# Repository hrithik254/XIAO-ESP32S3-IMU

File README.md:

An IMU with MPU9250 IMU and XAIO ESP32S3  # XIAO-ESP32S3-IMU

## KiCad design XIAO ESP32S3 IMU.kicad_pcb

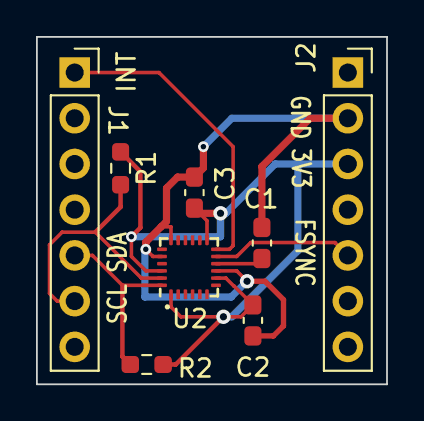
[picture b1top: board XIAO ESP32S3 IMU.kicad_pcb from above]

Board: 2 copper layers, 19.5 x 19.3 mm, 8 parts (0 on the bottom side), 7 nets.

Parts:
C1, C3: 0.1uF; C_0603_1608Metric_Pad1.08x0.95mm_HandSolder
C2: 10nF; C_0603_1608Metric_Pad1.08x0.95mm_HandSolder
J1: Pins1_7; PinSocket_1x07_P2.54mm_Vertical
J2: Pins8_14; PinSocket_1x07_P2.54mm_Vertical
R1, R2: 4K7; R_0603_1608Metric_Pad0.98x0.95mm_HandSolder
U2: MPU-9250; InvenSense_QFN-24_3x3mm_P0.4mm

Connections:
/3V3: C2.1, C3.1, J2.3, R1.1, R2.1, U2.1 (RESV_VDDIO), U2.8 (VDDIO), U2.13 (VDD), U2.22 (~CS)
/FSYNC: J2.5, U2.11 (FSYNC)
/INT: J1.1, U2.12 (INT)
/SCL: J1.6, R1.2, U2.23 (SCL/SCLK)
/SDA: J1.5, R2.2, U2.24 (SDA/MOSI)
GND: C1.2, C2.2, C3.2, J2.2, U2.9 (AD0/MISO), U2.18 (GND), U2.20 (RESV_GND)
unnamed: C1.1, U2.10 (REGOUT)

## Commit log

2023-08-16 gerber generation
2024-03-03 no changes
